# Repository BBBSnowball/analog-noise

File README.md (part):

"Completely analog" noise generator
===================================

A friends is very into analog synthesizers. I'm usually more on the digital side.
You can imagine the discussions we sometimes have about this ;-)

He recently baught [this drum synthesizer][1] that supposedly has "some digital
components" but he said that any passive module is "analog enough". What is a
passive module? Anything without a dedicated power supply, i.e. the only power
flowing into it is via its input signals.

Some time later, he mentioned that he doesn't know of any good analog noise generators.

Well.... let the trolling begin :-D

[1]: https://www.errorinstruments.com/a-85227938/bricky-format-standalone-box/po-passive-operator-drum-synth/

## Plan

- MCU
    - internal oscillator (for low power)
    - put into sleep until gate input is high enough
        - TODO: How to do hysteresis? STM32F072 can compare to internal 1.2V reference or 1/4, 1/2 or 3/4
          of that. We could switch between those to adjust threshold.
    - at least to ADC channels, fast enough to sample both inputs with >=50 kHz
    - CRC32 unit might be useful for generating the noise (basically an LFSR).
    - DAC would be great but PWM is ok (but more complex because of filter).
- power: diode rectifier, LDO, MLCC
    - maybe another MLCC on Vbat (if available), MLCC [seems to be good enough][cap-discharge]
- inputs:
    - 1x gate
        - comparator to wake up MCU (IC or something simple)
        - expect +-10 V / 1 kOhm at driver; add 100R on our side
    - 2x input: 10 kOhm and filter, to ADC
    - 1x output: amplify to +-10V if possible, 10 kOhm impedance should be ok for a passive module
- optional:
    - maybe an LED
        - sadly not WS2812 because of 1 mA quiescent current
        - Use high-efficiency LEDs and reduce the current a lot.
    - maybe a button, potentiometer or encoder
    - USB - for ~~programming~~ analog configuring and trolling
    - bootloader:
        - CH23V203: pull PB8 high with VUSB (voltage divider! and solder jumper) or add a button
        - STM32F072: pull BOOT0 high
    - TRNG
    - one or more touch areas, "Theremin", also mix into the noise (if we don't have a TRNG)
        - The MCU even has dedicated hardware for that. Nice! -> Still true after switching to STM.
    - IMS :-D
        - [LIS2DH12TR](https://jlcpcb.com/partdetail/Stmicroelectronics-LIS2DH12TR/C110926)
          is cheap and only consumes some uA. Well... I guess that means yes.
        - There aren't any basic parts in the sensor category, so extended parts fee is more
          than component cost.
        - Typical sample rate ("ODR/2") seems to be 10/2 Hz or 50/2 Hz but can be as high as 5/2 kHz,
          so we could probably use this for input (tilt, then double-tap).
        - We could react to disturbance. We had lots of fun with that feature of a spring reverb :-)
    - small epaper?
        - Doesn't look like a display (i.e. not digital). Can show function of current firmware.
        - Waveshare's 1.9'' epaper has I2C but that is 7-segment, not pixels. The others are as
          complicated as the one that we have used for the Framework 16 project (and they also use
          quite a lot of pins).
        - [This one](https://www.waveshare.com/product/displays/e-paper/2.13inch-touch-e-paper-hat.htm)
          has touch (only five points), maybe a suitable case. Communication is still SPI. Maybe as an optional
          feature instead of LEDs and touch. It is rather large.
- mechanical:
    - "analog noise generator with gate": shrink tube, put in the middle of a patch cable
    - "analog multiplier with gate": Eurorack module cover (3D printed or wood), glue PCB to its back, three jacks
    - 3D printed case in cable, with two parts that can be rotated to set a value
    - LQFP-48 is 9x9 mm with pins (7 mm for body). That is larger than I would like but smaller packages
      are more expensive.

[cap-discharge]: https://www.robotroom.com/Capacitor-Self-Discharge-2.html

- How much power do we have available?
    - 10 V / 1 kOhm is 10 mA. As we use an LDO, that's also true at 3.3 V.
    - MCU need 0.5 mA to 16 mA depending on frequency, so let's stick to lower frequencies.
    - output will provide up to 1 mA at 10 kOhm impedance (plus what the amplifier needs).
    - We should expect to see up to 15 V continuous because 10 V is more like the minimum and
      many modules go up to 1..2 V below there supply of 12 V or 15 V.
- How much delay after the gate is asserted? -> not updated for STM, yet
    - Startup time for oscillator alone is 2.5 ms. Internal HSI needs 10 us.
    - Let's expect a few ms overall and hope for the best.
    - It could be a lot less if gate rises slowly (we can start up before it reaches the
      threshold). In fact, that is our goal and that's why the threshold voltage is near
      the maximum.
- Any PCBs that we can use as reference or even copy?
    - https://github.com/metro94/FlappyBoard
    - I'm not sure which things on the board may be notices according to OHL but we will
      probably only copy the schematic anyway.
    - https://github.com/Jana-Marie/OtterPill
    - Use SY8201?
        - 0.4 mA quiescent current will be 3 mW at 7 V. LDO would waste 11 mW at 7 V.
        - We would have to use lower caps.
        - LDO is simpler+cheaper and good enough, we think.
    - Well, if we use neither SY8201 nor FUSB and we use STM32 symbol from Kicad libraries,
      there isn't anything to copy from OtterPill.
- Which LDO?
    - There don't seem to be any basic parts in category power.
    - More than 15 V (with some margin). Reasonable quiescent current.
    - 5 mA would be 60 mW.
    - [LR8321A-T33](https://www.lcsc.com/product-detail/Linear-Voltage-Regulators-LDO_LR-LR-LR8321A-T33_C5129918.html),
      [vendor page](https://www.lorysemi.com/product/80b8478f710f4a6b9008f729313d2654/a9d765514f14408ab45c6008f1d1d0b4):
      100 mA, 250 mW
- Pinout planning - assuming that we use the QFN28 package. -> This was for CH32.
    - fixed:
        - 4x power
        - 2x crystal
        - 2x BOOT0, nRST  (BOOT0 can be an output after startup)
        - 2x USB
        - 2x SWD ?
        - 1x WKUP?
    - usable:
        - PA1..PA7 (ADC)
        - PB0..PB1 (ADC)
            - PA2..PB1 are also used for the opamps.
            - Touch uses the ADC pins.
            - //Can all ADC inputs be connected to either of the two ADCs? -> We only have one for STM.
        - PA9
        - PA15
        - PB3..PB7
            - PB6 and PB7 are I2C1 (and PB5). PB6 is SCL, which can also be mapped to PB8. I2C is for IMS.
            - PB5 is `I2C_SMBA` (SMBus Alert), which we don't need.
        - summary: 9x ADC, 7x GPIO (including I2C)
    - needed:
        - 2x I2C
        - 1x wakeup+gate -> PA0 (WKUP and ADC0)
        - 2x input (ADC)
        - voltage doubler / inverter
          - 2x positive and negative output rail (ADC, so we know our usable range)
          - 1x input supply (ADC)
            (wakeup is connected to unfiltered gate, i.e. not the same as current voltage in capacitor)
          - 1x inverter for negative rail (PWM)
          - 1x doubler for positive rail (PWM)
          - 2x output signal (ADC)
          - (ADC signals for rails could be used as LED outputs if we don't use high-z and keep the ADC voltages below LED Vf.)
        - 1..2x output (TIM)
        - 1x VUSB detect (BOOT0 cannot be used as an input)
            - Could be the same as e.g. a touch key (which is then not usable while VUSB is present).
        - sum so far: 15 (7 ADC)
        - 0..1x touch (ADC)
        - 4x LED ?
            - [charlieplexing](https://en.wikipedia.org/wiki/Charlieplexing)
            - 12 LEDs with 4 pins. Do we need a resistor per LED? Or half the resistor on each pin?
            - Alternative: Bidir matrix with 8 LEDs.
            - We can use BOOT0 pin but not as three-state.
        - 0x button ?
        - 1x poti ?
- Pinout planning for STM32F072CBT6 (LQFP-48):
    - fixed:
        - 1: VBAT (nice - we have that available here)
        - 3,4: OSC32
        - 5,6: OSC
        - 7: NRST
        - 8,9: analog power
        - 14, 15: DAC
        - 23, 24: power
        - 32, 33: USB
        - 34: SWDIO
        - 35, 36: power
        - 37: SWCLK
        - 44: BOOT0
        - 47, 48: power
    - usable:
        - 2, 10, 11, 12, 13, 16, 17, 18, 19, 20, 21, 22, 26..31, 38..43, 45, 46
        - 26x ^^
    - comparator:
        - outputs are fixed
        - inputs can be on several pins or Vref (1.25V or 1/4, 2/4, 3/4 of that),
          Vref can be connected to negative input
        - COMP1: input is PA1, output is PA0, which is also WKUP
        - COMP output can also go to EXTI, which is also a wakeup source from most modes.
    - I2C:
        - PB10, PB11 (I2C2)
        - PB13, PB14 (I2C2)
        - PB6, PB7   (I2C1)
        - PB8, PB9   (I2C1)
    - SPI:
        - PA4..PA7 (SPI1)
        - PB10, ..?
        - PB12..PB15 (SPI2)
            - PB13: SCK, SCL  -> IMS also has them on the same pin.
            - PB14: MISO, SDA -> IMS has SDA and MOSI on the same pin.
        - PA15 or PB9, PB3..PB5 (SPI1)

### TODO

- Can CH32V2xx run its USB bootloader from internal crystal or should we add an external one?
    - Well, let's add the external one and hopefully not use it (but it doesn't really need
      more power than HSI, to be honest).
    - STM32F072 can definetely do it without the crystal.
- Low-power OpAmp for output or transistor amplifier?
    - Rail-to-rail would be useful. That should be easier with an integrated part.
    - There are lots of low power amplifiers, e.g. [LP358][LP358]. They are below 100 uA.
      Actually, we could tolerate a bit more than that. GBW is often not great but we amplify
      by 6x for audio so ~150 kHz should be fine (or less - depending on how much we filter
      our PWM anyway).
    - The cheapest LM321 on LCSC has 1.2 to 3 mA depending on VCC. That is a bit high but
      should work.
    - The cheapest LM358 on LSCS has below 1 mA even at 36 V. That's good. Output doesn't
      go up to positive rail even at very low current.
    - Cheapest with FET input on LCSC is TL072. It needs ~~a bit over 1 mA~~ per amplifier
      (so maybe try and use the 1x variant) and it goes to within 0.2 V of the rails at
      10 kOhm. Sounds good.
    - TL082 is similar but I just noticed that supply current is 1.4 to 2.8 mA per amplifier
      and that also goes for the TL072 (the figure from before was quiescent current).
    - Well, let's use one of them anyway. That's good enough.
    - We want TL072CDT because that's the only basic part in that category! Supply current is
      2.5 mA max but output swing is 1.5 V below the rails.
    - Actually, the [basic part LM324](https://jlcpcb.com/partdetail/Stmicroelectronics-LM324DT/C71035)
      is quite low-power. How did I miss that before? It will still be 1-3 mA because it has
      4 amplifiers.
    - Downside of LM324 is that its `V_OH` is 1.5 V below the upper rail.
- Can we make a simple TRNG? What sources of entropy do we have?
    - [Infinity Noise](https://github.com/waywardgeek/infnoise) has good documentation but
      3 opamps is a bit much for us.
    - Ring oscillators, e.g. [like this](https://github.com/stnolting/neoTRNG). This is more
      for FPGA but we could use the oscillators of the MCU.
    - Tie unused ADC inputs to half VCC with high impedance.
    - Onchip temperature sensor.
    - Mix in the unique ID.
    - Store previous seed in RTC memory.
    - IMS.
- Connect VBAT?
    - //It would be nice to have the RTC available but dedicated VBAT is only available on the
      larger packages.
    - Alternative: Not much connected to 3.3V supply, diode in series to LDO. Stop and standby
      don't use more current than RTC according to datasheet. Downside: It needs programming
      discipline and we have to power down anything that we connect to that supply (or
      power it through an IO pin).
    - It is available for STM. Yes, let's connect it.
- What do we do about negative voltages?
    - We will usually get a gate signal with 0 V and 10 V, I assume. And we have GND. We can add a
      negative voltage rail but it won't usually be charged.
    - That's not so great because our opamp won't be so great near the negative rail, which will
      be GND in our case.
    - Simple switched capacitor voltage inverter to at least have -2.9 V? -> Probably a good idea.
- How much capacity for power buffer? How to connect it?
    - //Long enough to provide useful time for RTC. MCU and IMS will draw some tens of uA.
        - Starting at 3.3 V. Normal operating range is down to 2.4 V. RTC can work down to
          1.8 V (when powered through VBAT).
        - Example: 1 uF = 50uA*t/(3.3V-2.4V) => t = 0.018 sec => not so great
    - STM32: 2 uA on Vbat with LSE. Works down to at least 1.65 V.
        - Example: 1 uF =  2uA*t/(3.3V-1.65V) => t = 0.8 sec => usable but not great
        - Typical values are more like 1 uA and half that at lower voltage, i.e. let's assume 2 sec.
        - We can use more capacity but we have to be smart about charging it, e.g. GPIO -> diode and resistor -> cap -> diode -> Vbat.
        - If we have 1% duty cycle, we should charge with 100x 2 uA, i.e. 200 uA. Ok, we could do that without controlling it with a GPIO.
          8 kOhm would achieve that but draw 400 uA when the cap is empty but we will lose some
          power through it when drawing current from the cap (but voltage drop is only 20 mV,
          i.e. not an issue and a diode would lose more power).
        - So... 100 nF on Vbat plus maybe 10 uF connected via 10 kOhm.
        - What can we use it for? Store random seed and wakup main MCU (but that needs main power
          anyway).
        - Ok, let's not put too much effort here: Use LSI instead of LSE (although we have no idea
          how much power that costs). 100 nF + 10 + 1 or 10 uF
    - Long enough to switch MCU to low-power mode, e.g. a few ms. Maybe long enough to continue
      working for a few ms to compensate startup delay.
        - Let's plan with 5 mA and 10 ms.
        - Voltage can go from 10 V to 5 V but that will be noticed in the output signal, of course.
        - That would be 10 uF. That is reasonable.
        - However... how long would it take to charge this? tau = 10 ms. Not great.
    - Another issue: We cannot set our gate threshold to 8 V because we will see less voltage
      while we are drawing power or even charging the capacitor.
        - If we draw 5 mA, we will see half the voltage. Not only for the gate but also for the
          capacitor. D'oh!
        - So... it would be good to limit ourselves to 3 mA and not much capacity.
        - The gate should have a large hysteresis.
    - Options?
        - Supply for MCU by DCDC (up to 3x more efficient).
            - If we find cheap DCDCs, we could have a step-down for the MCU, step-up for real 10 V
              and inverter for -10 V. The quiescent currents will add up so that is probably not
              feasible but we can try. -> but opamp would have to be even more power efficient.
            - Step-down: [TPS560200](https://jlcpcb.com/partdetail/TexasInstruments-TPS560200DBVR/C83671)
            - Suggested capacitors are rather high (10 uF) for most DCDCs.
        - Use less power for the MCU. It needs only 0.5 mA at low frequencies.
        - Voltage doubler (and maybe a voltage inverter from the higher voltage instead of MCU pin).
        - Generate output voltage from MCU pin (0 to 3.3V range, only passive filter).
        - Generate output voltage with h-bridge plus passive filter (power consumption to be determined).
            - Example: 10 kOhm plus 5 nF (and maybe 1 kOhm to output). tau=50 us (20 kHz). Current is 1 mA
              at 100 kHz according to Falstad.
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
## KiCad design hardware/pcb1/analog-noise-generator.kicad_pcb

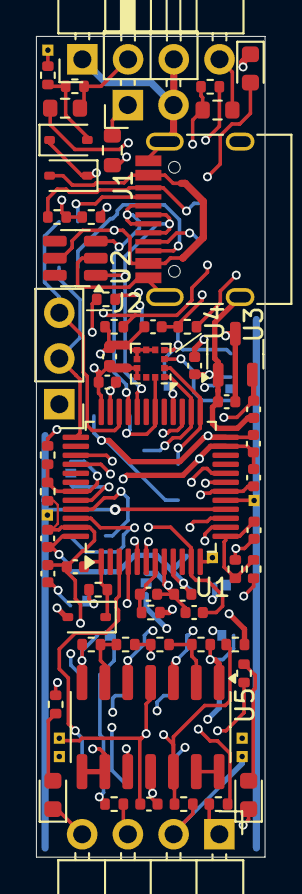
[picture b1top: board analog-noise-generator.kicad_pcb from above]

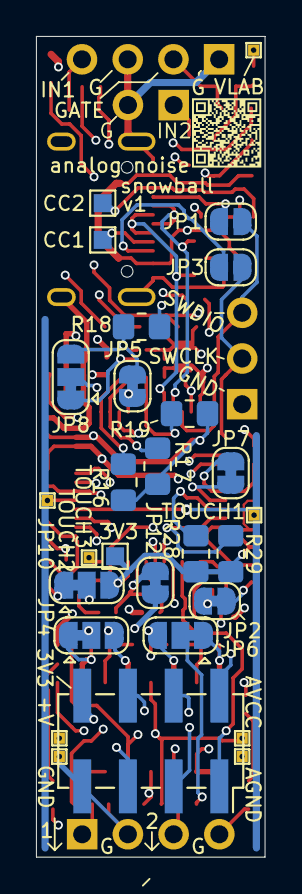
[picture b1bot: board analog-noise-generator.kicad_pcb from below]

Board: 4 copper layers, 12.7 x 45.6 mm, 90 parts (29 on the bottom side), 66 nets.

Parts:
C1, C2, C3, C4, C5, C11: 100n; C_0402_1005Metric
C6: 10u, 4V; C_0402_1005Metric
C8: 2u2, 4V; C_0402_1005Metric
C9: 10n; C_0402_1005Metric
C12: 100n_50V; C_0402_1005Metric
C13, C14, C15, C18: 220p; C_0402_1005Metric
C20, C21: 1u, 25V; C_0402_1005Metric
D1, D3, D4: D_SOD-323
D5: white; LED_0603_1608Metric
D6: yellow; LED_0603_1608Metric
D7: red; LED_0603_1608Metric
J1: USB_C_Receptacle_USB2.0; USB_C_Receptacle_HRO_TYPE-C-31-M-12
J2: Conn_01x03_Pin; PinHeader_1x03_P2.54mm_Vertical
J5, J6: Conn_01x04_Pin; PinHeader_1x04_P2.54mm_Horizontal
J7: Conn_01x02_Pin; PinHeader_1x02_P2.54mm_Horizontal
J9: Conn_02x04_Odd_Even; PinSocket_2x04_P2.54mm_Vertical_SMD
JP1, JP3: SolderJumper_2_Open; SolderJumper-2_P1.3mm_Open_RoundedPad1.0x1.5mm
JP2, JP5, JP7, JP12: SolderJumper_2_Bridged; SolderJumper-2_P1.3mm_Bridged_RoundedPad1.0x1.5mm
JP4, JP6, JP8, JP10: SolderJumper_3_Bridged12; SolderJumper-3_P1.3mm_Bridged12_RoundedPad1.0x1.5mm
NT1, NT2: NetTie_2; NetTie-2_SMD_Pad0.5mm
QR1: QR_git_3.8
R1, R2, R6, R9: 5.1k; R_0402_1005Metric
R3, R4, R7, R8, R13, R15, R20, R21, R22, R23, R24, R27, R30, R31, R32: 10k; R_0402_1005Metric
R5: 100R; R_0402_1005Metric
R10: 20k; R_0402_1005Metric
R14, R25, R26: 68k; R_0603_1608Metric
R16, R19: 10k; R_0805_2012Metric_Pad1.20x1.40mm_HandSolder
R17, R18, R28, R29: 4k7; R_0805_2012Metric_Pad1.20x1.40mm_HandSolder
R33: 1k; R_0402_1005Metric
R34, R35: 2k2; R_0402_1005Metric
TP1: CC1; TestPoint_Pad_1.0x1.0mm
TP2: CC2; TestPoint_Pad_1.0x1.0mm
TP3: VLAB; TestPoint_THTPad_small
TP4: +V; TestPoint_THTPad_small
TP6: TOUCH1; TestPoint_THTPad_small
TP7: TOUCH2; TestPoint_THTPad_small
TP8: TOUCH3; TestPoint_THTPad_small
TP9: GND; TestPoint_THTPad_small
TP10: AGND; TestPoint_THTPad_small
TP11: AVCC; TestPoint_THTPad_small
TP12: 3V3; TestPoint_Pad_1.0x1.0mm
U1: STM32F072CBTx; LQFP-48_7x7mm_P0.5mm
U2: USBLC6-2SC6; SOT-23-6
U3: LR8321A-T33; SOT-23-3
U4: LIS2DH12; LGA-12_2x2mm_P0.5mm
U5: LM324; SOIC-14_3.9x8.7mm_P1.27mm

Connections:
+3.3V: C2.1, C3.1, C4.1, C5.1, C8.1, C11.1, D4.2 (A), J9.8, JP10.3 (B), NT2.1, R8.2, R16.2, R17.2, R18.2, R19.2, R22.1, R28.2, R29.2, TP12.1, U1.9 (VDDA), U1.24 (VDD), U1.36 (VDDIO2), U1.48 (VDD), U3.2 (VO)
+8V: C20.1, C21.1, D1.1 (K), D3.1 (K), JP10.1 (A), R10.2, TP4.1, U3.3 (VI)
+BATT: C1.1, D4.1 (K), R4.2, U1.1 (VBAT)
/AGND: C12.2, JP12.2 (B), TP10.1, U5.11 (V-)
/AVCC: C12.1, JP10.2 (C), TP11.1, U5.4 (V+)
/BOOT0: JP7.2 (B), U1.44 (BOOT0)
/DAC1: JP4.3 (B), U1.14 (PA4), U5.3 (+)
/DAC2: JP6.3 (B), U1.15 (PA5), U5.5 (+)
/EPD_BUSY: J9.1, U1.3 (PC14)
/EPD_CS: J9.4, U1.4 (PC15)
/EPD_DC: J9.3, U1.6 (PF1)
/EPD_RES: J9.2, U1.5 (PF0)
/IMS_3V3: NT2.2, U4.9 (Vdd), U4.10 (Vdd_IO)
/IMS_GND: C14.2, NT1.1, U4.5 (RES), U4.6 (GND), U4.7 (GND), U4.8 (GND)
/IMS_INT: R19.1, U1.30 (PA9), U4.12 (INT1)
/IMS_SDI: JP5.2 (B), JP8.3 (B), R18.1, U4.4 (SDA/SDI)
/IMS_SDO: JP8.1 (A), U4.3 (SA0/SDO)
/IMS_nCS: R16.1, U1.25 (PB12), U4.2 (~CS)
/IN1: J6.4, R25.1
/IN1L: C13.1, R24.1, R25.2, U1.18 (PB0)
/IN2: J7.1, R26.1
/IN2L: C14.1, R26.2, R27.1, U1.19 (PB1)
/LED1: R33.1, U1.20 (PB2)
/LED2: R34.1, U1.40 (PB4)
/LED3: R35.1, U1.39 (PB3)
/MISO: JP8.2 (C), U1.27 (PB14)
/MOSI: J9.6, JP5.1 (A), U1.28 (PB15)
/NRST: C9.1, R8.1, U1.7 (NRST)
/OUT1: J5.1, R20.2
/OUT2: J5.3, R21.2
/SBU1: J1.A8 (SBU1), JP1.2 (B)
/SBU2: J1.B8 (SBU2), JP3.2 (B)
/SCK: J9.5, R17.1, U1.26 (PB13), U4.1 (SCL/SPC)
/SCL: R28.1, U1.45 (PB8)
/SDA: R29.1, U1.46 (PB9)
/SWCLK: J2.2, JP3.1 (A), U1.37 (PA14)
/SWDIO: J2.3, JP1.1 (A), U1.34 (PA13)
/TOUCH1: TP6.1, U1.16 (PA6)
/TOUCH2: TP7.1, U1.17 (PA7)
/TOUCH3: TP8.1, U1.12 (PA2)
/USB_D+: J1.A6 (D+), J1.B6 (D+), U1.33 (PA12), U2.3 (I/O2)
/USB_D-: J1.A7 (D-), J1.B7 (D-), U1.32 (PA11), U2.1 (I/O1)
/V+_sense: C15.1, R9.1, R10.1, U1.13 (PA3)
/VIN: D1.2 (A), R3.2, R5.2
/VIN': J6.2, R5.1, R14.2
/VIN_sense: C18.1, R14.1, R15.2, U1.11 (PA1)
/VUSB_DET: JP7.1 (A), R6.2, R7.2, U1.43 (PB7)
/Vmiddle: R24.2, R27.2, U5.8, U5.9 (-)
GND: C1.2, C2.2, C3.2, C4.2, C5.2, C6.2, C8.2, C9.2, C11.2, C13.2, C15.2, C18.2, C20.2, C21.2, D5.1 (K), D6.1 (K), D7.1 (K), J1.A1 (GND), J1.A12 (GND), J1.B1 (GND), J1.B12 (GND), J1.S1 (SHIELD), J2.1, J5.2, J5.4, J6.1, J6.3, J7.2, J9.7, JP12.1 (A), NT1.2, R1.2, R2.2, R7.1, R9.2, R15.1, R23.1, R30.2, R32.2, TP9.1, U1.8 (VSSA), U1.23 (VSS), U1.35 (VSS), U1.47 (VSS), U2.2 (GND), U3.1 (GND)
unnamed: D5.2 (A), R33.2
unnamed: D6.2 (A), R34.2
unnamed: D7.2 (A), R35.2
unnamed: J1.A5 (CC1), R1.1, TP1.1
unnamed: J1.B5 (CC2), R2.1, TP2.1
unnamed: C6.1, JP2.1 (A)
unnamed: JP2.2 (B), R4.1
unnamed: JP4.1 (A), R13.2, U5.1
unnamed: JP4.2 (C), R20.1
unnamed: JP6.1 (A), R31.2, U5.7
unnamed: JP6.2 (C), R21.1
unnamed: R3.1, TP3.1
unnamed: R13.1, R30.1, U5.2 (-)
unnamed: R31.1, R32.1, U5.6 (-)
unnamed: R22.2, R23.2, U5.10 (+), U5.12 (+)
unnamed: U5.13 (-), U5.14
VBUS: D3.2 (A), J1.A4 (VBUS), J1.A9 (VBUS), J1.B4 (VBUS), J1.B9 (VBUS), R6.1, U2.5 (VBUS)

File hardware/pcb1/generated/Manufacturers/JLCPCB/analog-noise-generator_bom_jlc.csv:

"Comment","Designator","Footprint","LCSC Part #"
"220p","C13,C14,C15,C18","C_0402_1005Metric","C1530"
"100n","C1,C2,C3,C4,C5,C11","C_0402_1005Metric","C1525"
"50V, 100.01 nF","C12","C_0402_1005Metric","C307331"
"1u, 25V","C20,C21","C_0402_1005Metric","C52923"
"2u2, 4V","C8","C_0402_1005Metric","C12530"
"10u, 4V","C6","C_0402_1005Metric","C15525"
"red","D7","LED_0603_1608Metric","C2286"
"white","D5","LED_0603_1608Metric","C2290"
"yellow","D6","LED_0603_1608Metric","C72038"
"~","D1,D3,D4","D_SOD-323","C191023"
"Conn_01x03_Pin","J2","PinHeader_1x03_P2.54mm_Vertical",""
"USB_C_Receptacle_USB2.0","J1","USB_C_Receptacle_HRO_TYPE-C-31-M-12","C165948"
"100R","R5","R_0402_1005Metric","C25076"
"1k","R33","R_0402_1005Metric","C11702"
"2k2","R34,R35","R_0402_1005Metric","C25879"
"5.1k","R1,R2,R6,R9","R_0402_1005Metric","C25905"
"10k","R3,R4,R7,R13,R15,R20,R21,R22,R23,R24,R27,R30,R31,R32","R_0402_1005Metric","C25744"
"20k","R10","R_0402_1005Metric","C25765"
"68k","R14,R25,R26","R_0603_1608Metric","C23231"
"LIS2DH12","U4","LGA-12_2x2mm_P0.5mm","C110926"
"LM324","U5","SOIC-14_3.9x8.7mm_P1.27mm","C71035"
"LR8321A-T33","U3","SOT-23-3","C5129918"
"STM32F072CBTx","U1","LQFP-48_7x7mm_P0.5mm","C81720"
"USBLC6-2SC6","U2","SOT-23-6","C5180279"

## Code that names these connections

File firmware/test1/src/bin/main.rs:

#![no_std]
#![no_main]

extern crate analog_noise_test1;
extern crate cortex_m_rt;
extern crate rtt_target;
extern crate usb_device;
extern crate usbd_serial;

use core::mem::MaybeUninit;

use analog_noise_test1::{dac, epd, ims, touch, usb_serial};
use analog_noise_test1::hal::{self, pac};
use analog_noise_test1::hal::delay::Delay;
use analog_noise_test1::hal::gpio::*;
use analog_noise_test1::hal::prelude::*;
use analog_noise_test1::spi::*;
use rtt_target::rprintln;

use cortex_m_rt::entry;

fn test_pwm(led2: gpiob::PB3<Input<Floating>>, led3: gpiob::PB4<Input<Floating>>, _tim2: pac::TIM2, tim3: pac::TIM3, rcc: &mut hal::rcc::Rcc, delay: &mut Delay) {
    let (_led2, led3) = cortex_m::interrupt::free(move |cs| {
        (
            led2.into_alternate_af2(cs),
            led3.into_alternate_af1(cs),
        )
    });

    //let pwm2 = hal::pwm::tim2(tim2, led2, rcc, 20u32.khz());
    let mut led3 = hal::pwm::tim3(tim3, led3, rcc, 20u32.khz());
    let max_duty = led3.get_max_duty();  // 2400
    led3.set_duty(max_duty / 2);
    led3.enable();
    for _ in 0..4 {
        for i in 0..max_duty {
            led3.set_duty(i);
            delay.delay_ms(1_u16);
        }
    }
}

#[entry]
fn main() -> ! {
    let channels = rtt_target::rtt_init! {
        up: {
            0: {
                size: 1024,
                name: "Terminal"
            }
            1: {
                size: 128,
                // skip data if necessary but only full blocks
                mode: rtt_target::ChannelMode::NoBlockSkip,
                name: "IMS"
            }
        }
        down: {
            0: {
                size: 16,
                name: "Terminal"
            }
            1: {
                size: 16,
                name: "dummy"
            }
        }
    };
    rtt_target::set_print_channel(channels.up.0);
    let num = 42;
    rprintln!("Answer: {}", num);


    let mut dp = pac::Peripherals::take().unwrap();
    let mut cp = cortex_m::peripheral::Peripherals::take().unwrap();
    dp.RCC.apb2enr.modify(|_, w| w.syscfgen().set_bit());  // Enable clock for SYSCFG (used for EXTI?)
    let mut rcc = dp
        .RCC
        .configure()
        .hsi48()
        .enable_crs(dp.CRS)
        .sysclk(48.mhz())
        .pclk(24.mhz())
        .freeze(&mut dp.FLASH);
    let gpioa = dp.GPIOA.split(&mut rcc);
    let gpiob = dp.GPIOB.split(&mut rcc);
    let gpioc = dp.GPIOC.split(&mut rcc);
    let gpiof = dp.GPIOF.split(&mut rcc);

    let mut delay = Delay::new(cp.SYST, &rcc);

    dac::test_dac(dp.DAC, gpioa.pa4, gpioa.pa5, dp.TIM6, &mut rcc);

    test_pwm(gpiob.pb3, gpiob.pb4, dp.TIM2, dp.TIM3, &mut rcc, &mut delay);

    let spi = TimesharedSpi::new(gpiob.pb13, gpiob.pb14, gpiob.pb15, dp.SPI2, &mut rcc);

    // copy SPI into static memory because it will be used by an interrupt handler
    static mut SPI: MaybeUninit<TimesharedSpi> = MaybeUninit::uninit();
    let spi = unsafe { SPI.write(spi) };

    if true {
        let pb12 = gpiob.pb12;  // extract here to avoid moving gpiob into the closure
        let cs = cortex_m::interrupt::free(move |cs| {
            pb12.into_push_pull_output(cs)
        });
        let spidev = spi.make_device(cs);

        let mut ims = ims::IMS::new(spidev, gpioa.pa9);
        if let Err(err) = ims::test_ims(&mut ims) {
            rprintln!("ERROR: {:?}", err);
        }

        touch::test_touch(dp.TSC, &mut rcc, gpioa.pa6, gpioa.pa7, gpioa.pa2, gpioa.pa0);

        ims::start_writing_to_rtt(ims, channels.up.1, &mut dp.SYSCFG, &mut dp.EXTI, &mut cp.NVIC);
    }

    if true {
        let pc15 = gpioc.pc15;
        let cs = cortex_m::interrupt::free(move |cs| {
            pc15.into_push_pull_output(cs)
        });
        // The IMS may be using the SPI. It runs in an interrupt, so we can simply wait for it to be done.
        // We have to do this in a wrapper around the SpiDevice because the display library won't tell us
        // the SPI error code.
        let spidev = RepeatWhenBusy::new(spi.make_device(cs));

        let mut epd = epd::EpaperDisplay::new(
            spidev, gpiof.pf0, gpiof.pf1, gpioc.pc14, &mut delay);
        if let Err(err) = epd::test_epd(&mut epd, &mut delay) {
            rprintln!("ERROR: {:?}", err);
        }
    }

    usb_serial::main(usb_serial::UsbHardware {
        led_pin: gpiob.pb2,
        pin_dm: gpioa.pa11,
        pin_dp: gpioa.pa12,
        usb: dp.USB,
    });
}

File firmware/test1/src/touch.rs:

// TOUCH1, PA6, TSC_G2_IO3
// TOUCH2, PA7, TSC_G2_IO4
// TOUCH3, PA2, TSC_G1_IO3

use crate::hal::{
    gpio::*,
    gpio::gpioa::*,
    pac,
    rcc::Rcc,
};
use rtt_target::rprintln;

pub fn test_touch(tsc: pac::TSC, rcc: &mut Rcc, touch1: PA6<Input<Floating>>, touch2: PA7<Input<Floating>>, touch3: PA2<Input<Floating>>, pa0: PA0<Input<Floating>>) {
    let mut tsc = crate::hal::tsc::Tsc::tsc(tsc, rcc, None);
    let (mut touch1, mut touch2, mut touch3, mut pa0) = cortex_m::interrupt::free(move |cs| {
        (
            touch1.into_alternate_af3(cs),
            touch2.into_alternate_af3(cs),
            touch3.into_alternate_af3(cs),
            pa0.into_alternate_af3(cs),
        )
    });
    tsc.setup_sample_group(&mut touch2);
    tsc.setup_sample_group(&mut pa0);
    tsc.enable_channel(&mut touch1);
    tsc.enable_channel(&mut touch3);
    tsc.start();
    for _ in 0..4 {
        if let Ok(_) = tsc.acquire() {
            //rprintln!("TOUCH: {}, {}, {}", tsc.read(&mut touch1).unwrap(), tsc.read(&mut touch2).unwrap(), tsc.read(&mut touch3).unwrap());
            rprintln!("TOUCH: {}, {}", tsc.read(&mut touch1).unwrap(), tsc.read(&mut touch3).unwrap());
        }
    }
}

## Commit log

2024-06-05 initial plan
2024-06-07 add some simulations
2024-06-08 evaluate other options for MCU
2024-06-10 start with PCB
2024-06-11 fix some violations
2024-06-11 continue
2024-06-11 move USB connector to board edge
    We had it in the middle to achieve low thickness near the edges
    but that's no good if we want it to be usable in any kind of case
    (including shrink tube).
2024-06-11 shorten the board a bit
2024-06-12 remove negative voltage, add more LCSC part numbers, connect opamps
2024-06-16 start routing
2024-06-16 move all top parts onto PCB
2024-06-16 move PCB files
2024-06-16 copy Kibot files from Heizung project
2024-06-16 fix ERC issues
2024-06-16 generate files for JLC
2024-06-20 switch to four layers and continue routing
2024-06-21 finish routing
2024-06-21 improve silk
2024-06-23 add some LEDs
2024-06-28 add testpoint for 3.3V
2024-06-28 generate PCB files
2024-06-28 fix some issues for JLC
    - increase some clearances that were marked as "danger" in their DFM
    - change value of C12, so it won't be grouped with the incompatible 100 nF caps
    - add image to README
    - rotate U2 in CPL file
2024-07-19 add first test firmware
2024-07-19 try to add defmt-rtt
    This doesn't work so well because we
    cannot apply our bootloader workarounds
    when running under probe-rs and we
    couldn't get OpenOCD to read from RTT.
2024-07-19 use semihosting instead of RTT
2024-07-19 add TODOs, update README
2024-07-20 read data from IMS
2024-07-20 try to use RTT for custom data
    OpenOCD finds the RTT control block and
    often it prints some data to the TCP socket
    but that seems to be some random
    memory rather than the buffer.
2024-07-20 fixup: last argument for `monitor rtt setup` was wrong
2024-07-20 add graph of IMS values via RTT
2024-07-20 use RTT for serial console, as well (instead of semihosting)
2024-07-20 start testing touch
2024-07-20 test PWM for one LED
2024-07-20 add TODOs
2024-07-21 move main into bin, so we can have more than one binary
2024-07-21 first test of DAC
2024-07-21 fixup for build script
2024-07-21 fix some warnings
2024-07-21 enable debug info for release builds
2024-07-21 use builtin waveform generators for DAC (triangle and noise)
2024-07-21 change main2 to use less power
2024-08-03 add sine wave with some noise
2024-08-03 add more exotic waveforms
2024-08-03 add errata for output filter
2024-08-22 set default Rust toolchain
2024-08-22 implement DelayNs, GPIO and SPI for embedded-hal 1.0.0
2024-08-22 first implementation of epaper (untested)
2024-08-22 hal should implement SpiBus instead of SpiDevice
2024-08-22 use embedded-hal-bus to share the SPI
2024-08-22 retry SPI access for epaper if IMS is using the bus
2024-08-22 clean up
2024-08-22 copy SPI instance into static memory for use in interrupt handler
2024-08-22 enable size optimization for debug builds
2024-08-22 fix warning
2024-08-22 optimize binary size some more
